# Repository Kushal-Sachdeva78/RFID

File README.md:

# RFID Entry-Exit System for Vasant Valley School
Tap a school ID card to log attendance and laptop loans: ESP32 reader, FastAPI backend, web dashboard. For schools and makers.
```bash
cd rfid_system/backend && pip install -r requirements.txt && uvicorn main:app --reload   # use a venv, see rfid_system/GETTING_STARTED.md
```
<!-- DEMO: record a 5-10 s GIF of a card tap appearing on the dashboard, save as docs/demo.gif, then replace this line with  -->

A prototype of an RFID-based attendance, entry-exit, and laptop-borrowing system
built around the school's existing ID cards: ESP32 firmware with an RC522 reader
and TFT status display, a custom KiCad PCB, a FastAPI backend with a test suite,
and a web dashboard with optional Firebase mirroring.

## Motivation

At Vasant Valley School, attendance is marked manually by class teachers,
latecomers wait in a morning "late line" for manual strike marking, student
exits run on paper sign-out sheets, and borrowing a laptop needs a paper chit
signed across several flights of stairs. This project prototypes a replacement:
students and staff tap their existing ID cards, and the system records who
arrived, when, whether they were late, which way they are authorised to travel
home, and who is holding which laptop.

## What is in this repo

| Component | Path | What it does |
| --- | --- | --- |
| ESP32 firmware | `Main.ino` | Reads RC522 taps, keeps a real clock over NTP (with a simulated fallback), renders a status card, weekly grid, and entry/exit banner on the ILI9341 TFT, and posts each scan to the backend over Wi-Fi with retry and an offline buffer. Pin assignments match the fabricated board. |
| Backend service | `rfid_system/backend` | A FastAPI REST API covering health, roster, attendance events (entry/exit direction and second-resolution lateness), an office manual fallback, three-strike teacher notification, and laptop borrowing. Pydantic v2, timezone-aware, a swappable storage layer, role-scoped API keys, and a pytest suite. |
| Web dashboard | `rfid_system/frontend` | A static dashboard showing the roster, attendance events with direction, a gate exit-authorization banner, manual entry, and a laptop borrowing panel. Optional Firebase mirroring of manual scans. |
| PCB design | `RFID KICAD/` | Full KiCad schematic and board layout integrating the ESP32 DevKit V1, RFID reader, display, buzzer, power switch, and battery holder, with exported Gerbers in `RFID KICAD/RFID_PCB/`. |

## Features

- Attendance to the second against a real clock, with the 08:05 cutoff and bus
  riders exempt from lateness. A repeat tap does not double-mark attendance.
- Entry and exit logging on a single gate reader (a per-day toggle), with the
  guard-facing display showing whether a departing student may walk, go by car,
  or take the bus.
- An office manual fallback for a forgotten or lost card, flagged manual and
  attributed to the staff member.
- Three late days in a learning cycle notify the class teacher through a
  pluggable notifier (a file/stdout default, or SMTP from environment
  variables). No credentials are committed.
- Laptop borrowing with a full state machine: a student requests, a teacher
  approves or denies, a tech-lab helper issues a numbered unit and records the
  return, and the dashboard shows outstanding loans and how long each is held.

## Hardware

| Component | Purpose |
| --- | --- |
| ESP32 DevKit V1 | Wi-Fi microcontroller running the firmware |
| RC522 RFID module (SPI) | Scans ID cards |
| ILI9341 320x240 TFT | Shows the scan result, lateness, direction, and transport authorization |
| Buzzer | Audible scan feedback |
| Custom PCB | Integrates the components (KiCad sources and Gerbers in this repo) |

The firmware pin defines match the nets on the fabricated board (RC522 SS on
GPIO14 and RST on GPIO27; TFT CS on GPIO5, DC on GPIO21, RST on GPIO22; buzzer on
GPIO15; shared SPI on GPIO18/23/19). Verify with a continuity check before
flashing a unit.

## Getting started

To run the software on a laptop with no hardware, follow
[`rfid_system/GETTING_STARTED.md`](rfid_system/GETTING_STARTED.md): it covers the
backend and its tests, the dashboard, compiling the firmware with `arduino-cli`,
the laptop borrowing flow, and optional Firebase setup.

Continuous integration (`.github/workflows/ci.yml`) runs the backend tests and a
firmware compile for the ESP32 DevKit V1 on every push.

## Status

Implemented in this prototype: the firmware (real clock, Wi-Fi posting, offline
buffer, corrected pins); the backend (attendance with direction and lateness,
manual fallback, three-strike notification, laptop borrowing) with a pytest
suite; the dashboard; and the complete PCB design.

Not yet done: Firebase Auth so the optional Firestore mirror can be enabled,
on-device roster caching so the gate can identify all cards while offline, and
real per-user authentication in place of the prototype role keys.

## Developed by

**Kushal Sachdeva**, Vasant Valley School

More of my work: [github.com/Kushal-Sachdeva78](https://github.com/Kushal-Sachdeva78),
including [autonomous RoboCup soccer robots](https://github.com/Kushal-Sachdeva78/VVS-Ballers-RoboCup)
and [EnerJee](https://github.com/Kushal-Sachdeva78/EnerJee), a renewable energy
planning platform.

## License

This project is licensed under the MIT License. See [LICENSE](LICENSE) for details.

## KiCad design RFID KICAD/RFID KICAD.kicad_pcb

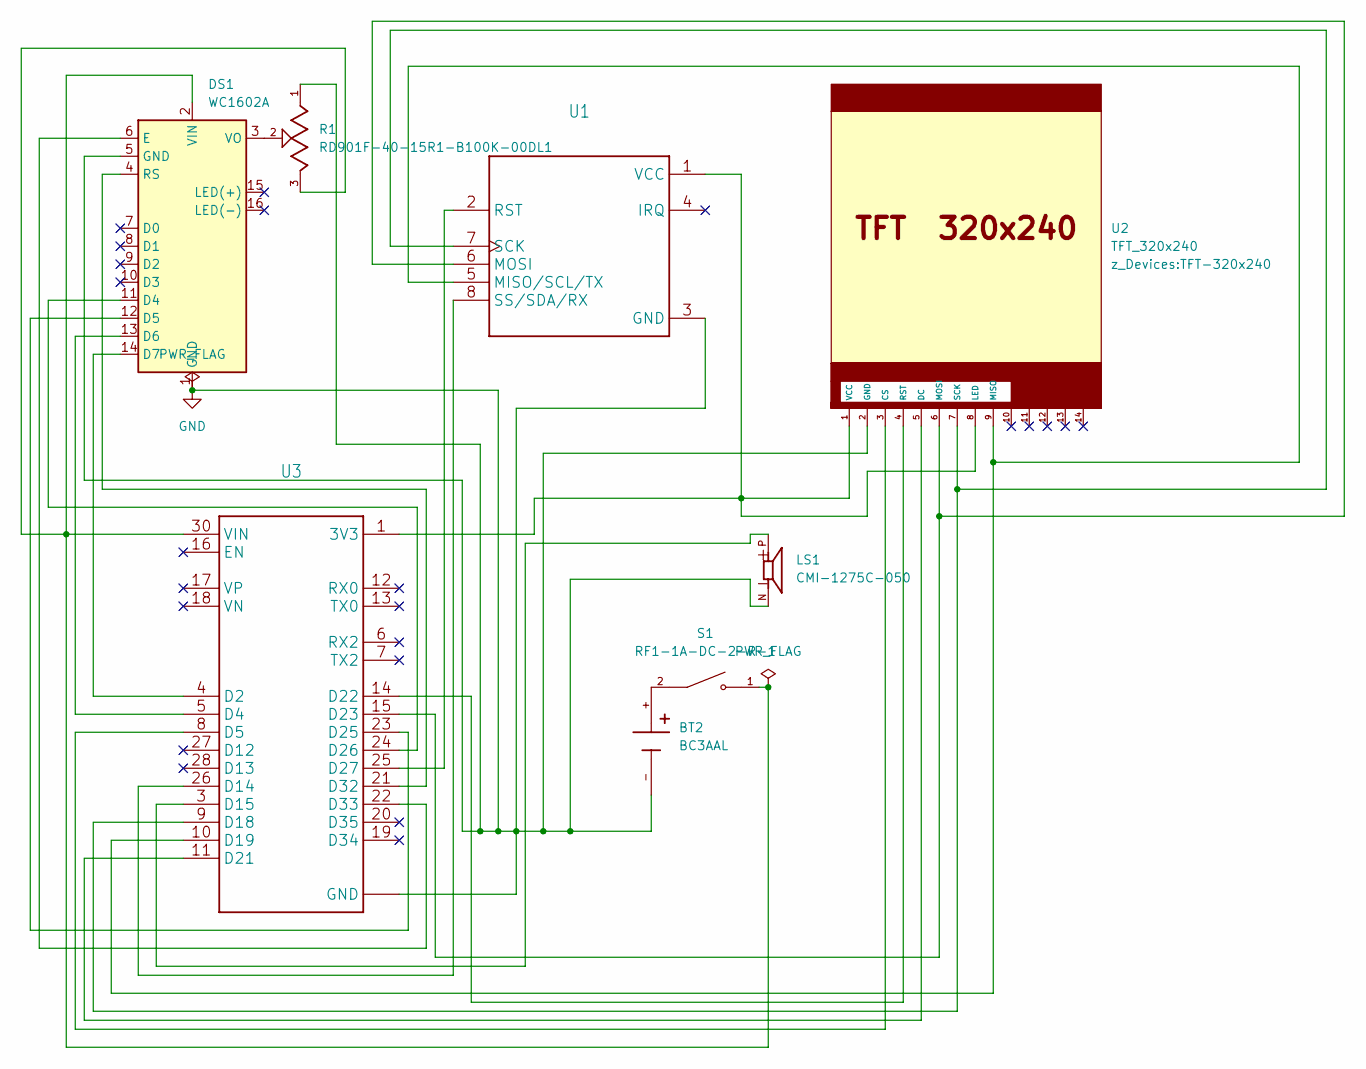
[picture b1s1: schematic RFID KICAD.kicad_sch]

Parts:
BT2: BC3AAL; BAT_BC3AAL; PARTREV J
DS1: WC1602A
LS1: CMI-1275C-050; CUI_CMI-1275C-050
R1: RD901F-40-15R1-B100K-00DL1; POT_RD901F-40-15R1-B100K-00DL1; PARTREV 10/5/23
S1: RF1-1A-DC-2-R-1; SW_RF1-1A-DC-2-R-1; PARTREV B
U1: MODULE_CEG006900
U2: TFT_320x240; TFT-320x240
U3: MODULE_ESP32_DEVKIT_V1

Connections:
GND: BT2.-, DS1.1 (GND), DS1.5 (GND), LS1.N, R1.1, U1.3 (GND), U2.2 (GND), U3.2 (GND), U3.29 (GND)
unnamed: BT2.+, S1.2
unnamed: DS1.11 (D4), U3.24 (D26)
unnamed: DS1.12 (D5), U3.23 (D25)
unnamed: DS1.13 (D6), U3.5 (D4)
unnamed: DS1.14 (D7), U3.4 (D2)
unnamed: DS1.6 (E), U3.22 (D33)
unnamed: DS1.4 (RS), U3.21 (D32)
unnamed: DS1.2 (VIN), R1.3, S1.1, U3.30 (VIN)
unnamed: DS1.3 (VO), R1.2
unnamed: U1.5 (MISO/SCL/TX), U2.9 (MISO), U3.10 (D19)
unnamed: U1.6 (MOSI), U2.6 (MOSI), U3.15 (D23)
unnamed: U1.2 (RST), U3.25 (D27)
unnamed: U1.7 (SCK), U2.7 (SCK), U3.9 (D18)
unnamed: U1.8 (SS/SDA/RX), U3.26 (D14)
unnamed: U1.1 (VCC), U2.1 (VCC), U2.8 (LED), U3.1 (3V3)
unnamed: U2.3 (CS), U3.8 (D5)
unnamed: U2.5 (DC), U3.11 (D21)
unnamed: U2.4 (RST), U3.14 (D22)
unnamed: LS1.P, U3.3 (D15)

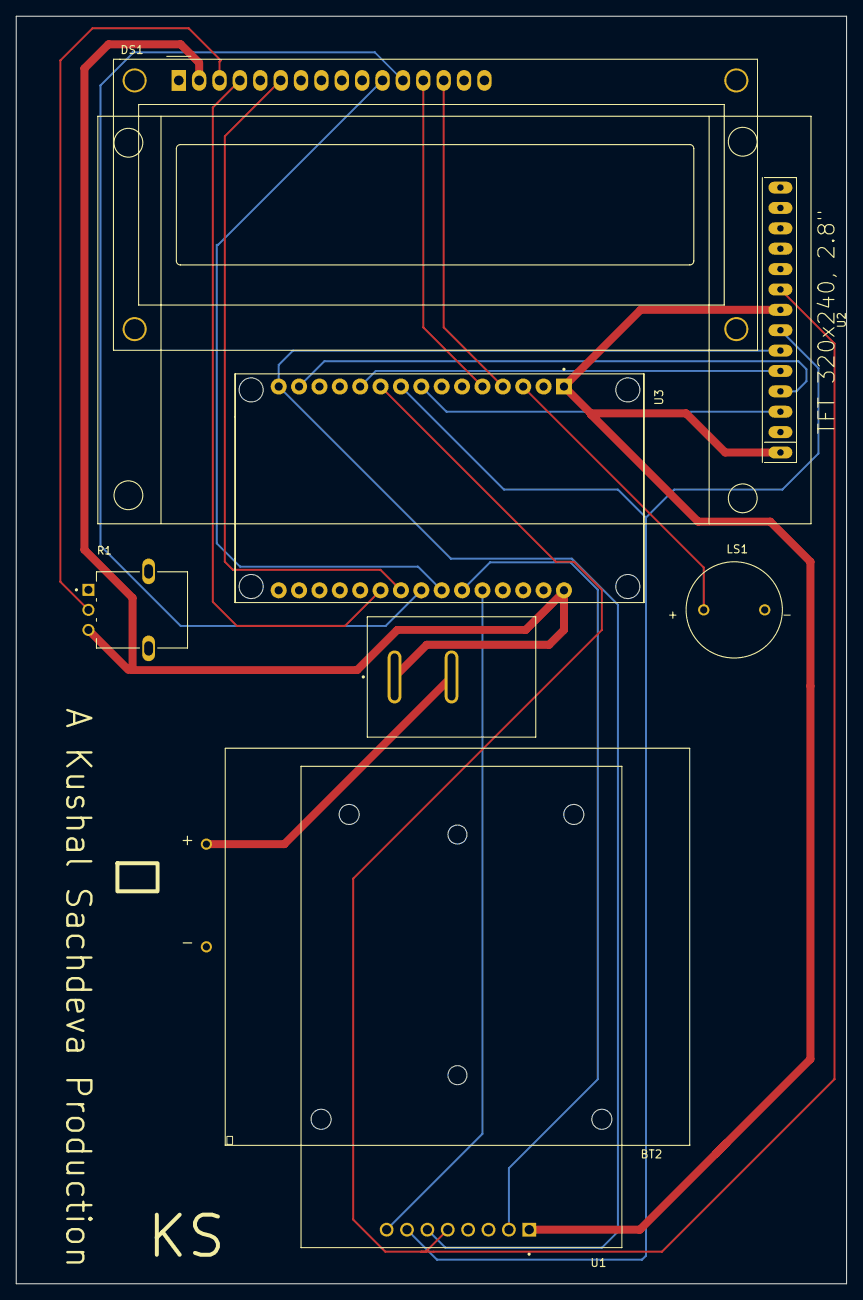
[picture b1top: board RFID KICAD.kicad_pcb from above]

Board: 2 copper layers, 103.5 x 158.0 mm, 8 parts (0 on the bottom side), 20 nets.

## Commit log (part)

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2025-11-08 Add full-stack support for ESP32 RFID system
2025-11-08 Refine documentation for software setup
2025-11-08 Clarify manual status options in laptop setup guide
2025-11-08 Add SPI screen preview and roster metadata to dashboard
2025-11-09 Support offline dashboard testing and update docs
2025-11-09 Create Teensy-focused TFT attendance firmware

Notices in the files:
README.md:
License: MIT
